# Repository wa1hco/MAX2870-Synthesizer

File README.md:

# Synthesizer
30 ro 6000 MHz frequency synthesizer based on MAX2870 chip

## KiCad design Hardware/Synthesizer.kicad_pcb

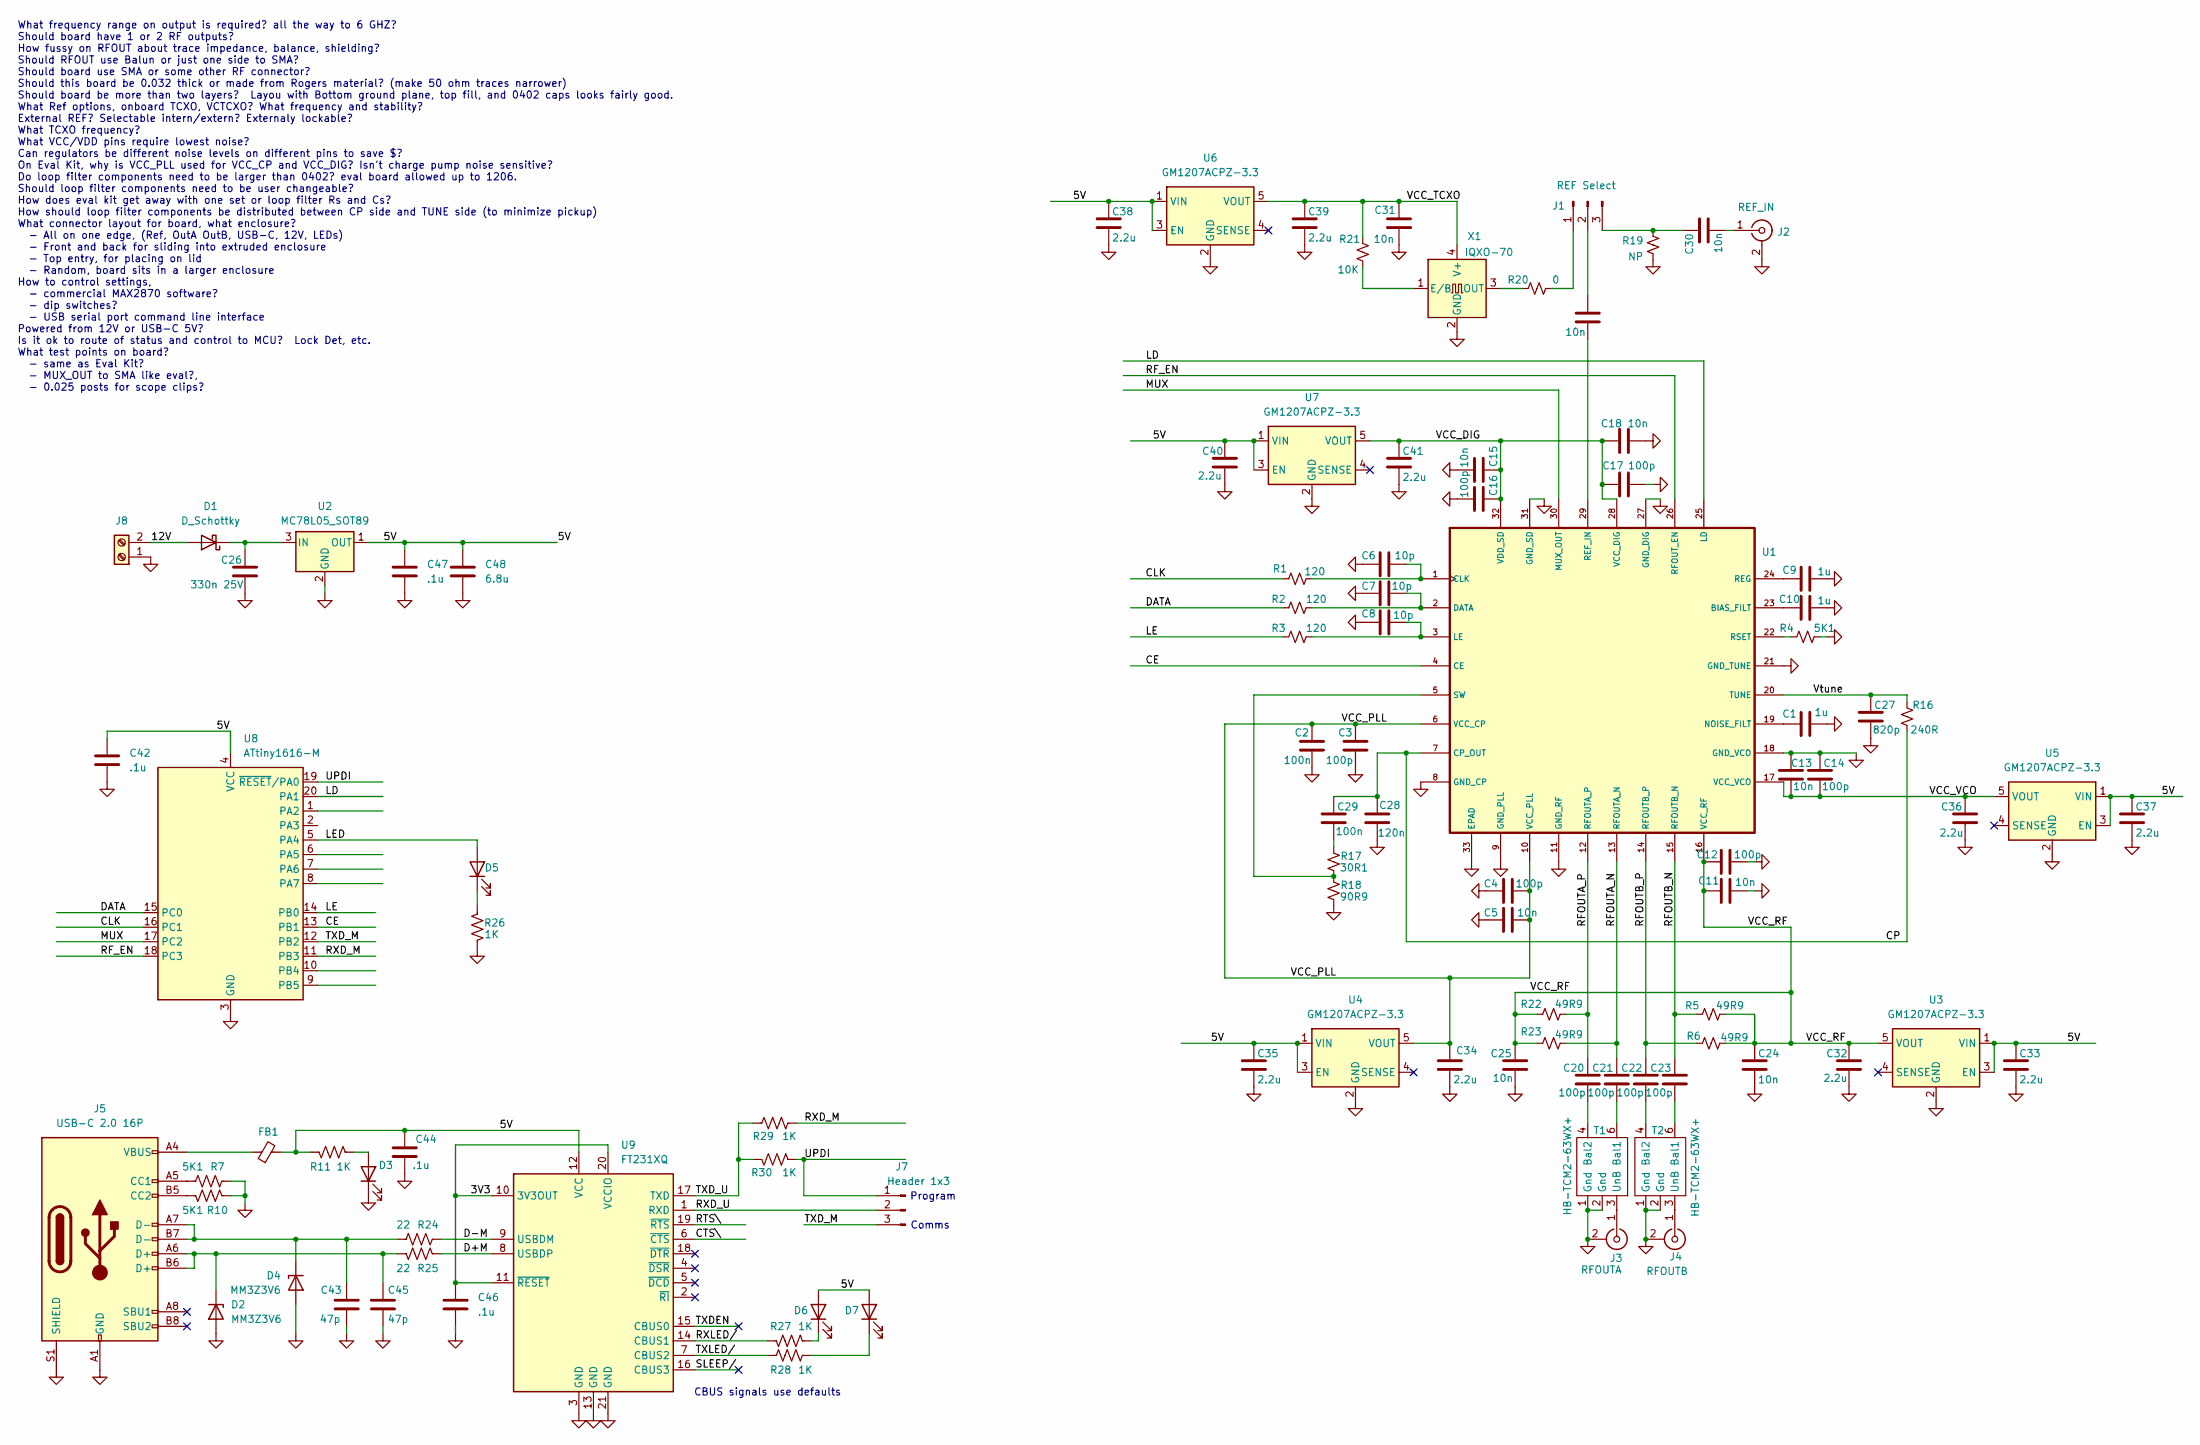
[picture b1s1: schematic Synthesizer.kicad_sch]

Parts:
C1, C9, C10: 1u; Cap_0402
C2, C29: 100n; Cap_0402
C3, C4, C12, C14, C16, C17, C20, C21, C22, C23: 100p; Cap_0402
C5, C11, C13, C15, C18, C19, C24, C25, C30, C31: 10n; Cap_0402
C6, C7, C8: 10p; Cap_0402
C26: 330n 25V; C_0603_1608Metric
C27: 820p; Cap_0402
C28: 120n; Cap_0402
C32, C33, C34, C35, C36, C37, C38, C39, C40, C41: 2.2u; Cap_0402
C42, C44, C46, C47: .1u; Cap_0402; LCSC C14663
C43, C45: 47p; Cap_0402; LCSC C1671
C48: 6.8u; C_0603_1608Metric; LCSC C338096
D1: D_Schottky; D_0603_1608Metric; LCSC C143772
D2, D4: MM3Z3V6; D_SOD-323; LCSC C116949
D3, D5: White; LED_0402_1005Metric; LCSC C2290
D6, D7: Yellow; LED_0402_1005Metric; LCSC C72038
FB1: FerriteBead_Small; L_0805_2012Metric; LCSC C1017
J1: REF Select; PinHeader_1x03_P2.54mm_Vertical; LCSC C6332196
J2: REF_IN; SMA_Samtec_SMA-J-P-H-ST-EM1_EdgeMount
J3: RFOUTA; SMA_Samtec_SMA-J-P-H-ST-EM1_EdgeMount
J4: RFOUTB; SMA_Samtec_SMA-J-P-H-ST-EM1_EdgeMount
J5: USB-C 2.0 16P; USB_C_Receptacle_G-Switch_GT-USB-7010ASV; LCSC C2988369
J7: Header 1x3; PinHeader_1x03_P2.54mm_Vertical; LCSC C6332196
J8: Screw_Terminal_01x12; TerminalBlock_TE_282834-2_1x02_P2.54mm_Horizontal; LCSC C5188451
R1, R2, R3: 120; Res_0402
R4: 5K1; Res_0402
R5, R6, R22, R23: 49R9; Res_0402
R7, R10: 5K1; Res_0402; LCSC C23186
R11, R26, R27, R28, R29, R30: 1K; Res_0402; LCSC C21190
R16: 240R; Res_0402
R17: 30R1; Res_0402
R18: 90R9; Res_0402
R19: NP; Res_0402
R20: 0; Res_0402
R21: 10K; Res_0402
R24, R25: 22; Res_0402; LCSC C23345
T1, T2: HB-TCM2-63WX+
U1: QFN-32-1EP_5x5mm_P0.5mm_EP3.1x3.1mm
U2: MC78L05_SOT89; SOT-89-3; LCSC C42738
U3, U4, U5, U6, U7: GM1207ACPZ-3.3; SOT-23-5
U8: ATtiny1616-M; VQFN-20-1EP_3x3mm_P0.4mm_EP1.7x1.7mm; LCSC C507118
U9: FT231XQ; QFN-20-1EP_4x4mm_P0.5mm_EP2.5x2.5mm; LCSC C132159
X1: IQXO-70; Oscillator_SMD_IQD_IQXO70-4Pin_7.5x5.0mm

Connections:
/3V3: C46.1, U9.10 (3V3OUT), U9.11 (~RESET), U9.20 (VCCIO)
/5V: C33.1, C35.1, C37.1, C38.1, C40.1, C42.1, C44.1, C47.1, C48.1, D6.2 (A), D7.2 (A), FB1.2, R11.2, U2.1 (OUT), U3.1 (VIN), U3.3 (EN), U4.1 (VIN), U4.3 (EN), U5.1 (VIN), U5.3 (EN), U6.1 (VIN), U6.3 (EN), U7.1 (VIN), U7.3 (EN), U8.4 (VCC), U9.12 (VCC)
/12V: D1.2 (A), J8.2
/CE: U1.4 (CE), U8.13 (PB1)
/CLK: R1.1, U8.16 (PC1)
/CP: C28.1, C29.1, R16.1, U1.7 (CP_OUT)
/CTS\: U9.6 (~CTS)
/D+M: R25.1, U9.8 (USBDP)
/D-M: R24.1, U9.9 (USBDM)
/DATA: R2.1, U8.15 (PC0)
/LD: U1.25 (LD), U8.20 (PA1)
/LE: R3.1, U8.14 (PB0)
/LED: D5.2 (A), U8.5 (PA4)
/MUX: U1.30 (MUX_OUT), U8.17 (PC2)
/RFOUTA_N: C21.1, R23.2, U1.13 (RFOUTA_N)
/RFOUTA_P: C20.1, R22.2, U1.12 (RFOUTA_P)
/RFOUTB_N: C23.1, R5.1, U1.15 (RFOUTB_N)
/RFOUTB_P: C22.1, R6.1, U1.14 (RFOUTB_P)
/RF_EN: U1.26 (RFOUT_EN), U8.18 (PC3)
/RTS\: U9.19 (~RTS)
/RXD_M: R29.2, U8.11 (PB3)
/RXD_U: J7.2, U9.1 (RXD)
/RXLED/: R27.1, U9.14 (CBUS1)
/SLEEP/: U9.16 (CBUS3)
/TXDEN: U9.15 (CBUS0)
/TXD_M: J7.3, U8.12 (PB2)
/TXD_U: R29.1, R30.1, U9.17 (TXD)
/TXLED/: R28.1, U9.7 (CBUS2)
/UPDI: J7.1, R30.2, U8.19 (~RESET/PA0)
/VCC_DIG: C15.1, C16.1, C17.1, C18.1, C41.1, U1.28 (VCC_DIG), U1.32 (VDD_SD), U7.5 (VOUT)
/VCC_PLL: C2.2, C3.2, C4.1, C5.1, C34.1, U1.6 (VCC_CP), U1.10 (VCC_PLL), U4.5 (VOUT)
/VCC_RF: C11.1, C12.1, C24.1, C25.1, C32.1, R5.2, R6.2, R22.1, R23.1, U1.16 (VCC_RF), U3.5 (VOUT)
/VCC_TCXO: C31.2, C39.1, R21.2, U6.5 (VOUT), X1.4 (V+)
/VCC_VCO: C13.1, C14.2, C36.1, U1.17 (VCC_VCO), U5.5 (VOUT)
/Vtune: C27.1, R16.2, U1.20 (TUNE)
GND: C1.2, C2.1, C3.1, C4.2, C5.2, C6.1, C7.1, C8.1, C9.2, C10.2, C11.2, C12.2, C13.2, C14.1, C15.2, C16.2, C17.2, C18.2, C24.2, C25.2, C26.2, C27.2, C28.2, C31.1, C32.2, C33.2, C34.2, C35.2, C36.2, C37.2, C38.2, C39.2, C40.2, C41.2, C42.2, C43.2, C44.2, C45.2, C46.2, C47.2, C48.2, D2.2 (A), D3.1 (K), D4.2 (A), J2.2 (Ext), J3.2 (Ext), J4.2 (Ext), J5.A1 (GND), J5.A12 (GND), J5.B1 (GND), J5.B12 (GND), J5.S1 (SHIELD), J8.1, R4.2, R7.1, R10.1, R18.2, R19.2, R26.2, T1.1 (Gnd), T1.2 (Gnd), T2.1 (Gnd), T2.2 (Gnd), U1.8 (GND_CP), U1.9 (GND_PLL), U1.11 (GND_RF), U1.18 (GND_VCO), U1.21 (GND_TUNE), U1.27 (GND_DIG), U1.31 (GND_SD), U1.33 (EPAD), U2.2 (GND), U3.2 (GND), U4.2 (GND), U5.2 (GND), U6.2 (GND), U7.2 (GND), U8.3 (GND), U8.21 (GND), U9.3 (GND), U9.13 (GND), U9.21 (GND), X1.2 (GND)
unnamed: C29.2, R17.1
unnamed: C26.1, D1.1 (K), U2.3 (IN)
unnamed: C45.1, D2.1 (K), J5.A6 (D+), J5.B6 (D+), R25.2
unnamed: D3.2 (A), R11.1
unnamed: C43.1, D4.1 (K), J5.A7 (D-), J5.B7 (D-), R24.2
unnamed: D5.1 (K), R26.1
unnamed: D6.1 (K), R27.2
unnamed: D7.1 (K), R28.2
unnamed: FB1.1, J5.A4 (VBUS), J5.A9 (VBUS), J5.B4 (VBUS), J5.B9 (VBUS)
unnamed: J1.1, R20.2
unnamed: C19.2, J1.2
unnamed: C30.1, J1.3, R19.1
unnamed: C30.2, J2.1 (In)
unnamed: J3.1 (In), T1.3 (UnB)
unnamed: J4.1 (In), T2.3 (UnB)
unnamed: J5.A5 (CC1), R7.2
unnamed: J5.B5 (CC2), R10.2
unnamed: C21.2, T1.6 (Bal1)
unnamed: C20.2, T1.4 (Bal2)
unnamed: C23.2, T2.6 (Bal1)
unnamed: C22.2, T2.4 (Bal2)
unnamed: C10.1, U1.23 (BIAS_FILT)
unnamed: C6.2, R1.2, U1.1 (CLK)
unnamed: C7.2, R2.2, U1.2 (DATA)
unnamed: C8.2, R3.2, U1.3 (LE)
unnamed: C1.1, U1.19 (NOISE_FILT)
unnamed: C19.1, U1.29 (REF_IN)
unnamed: C9.1, U1.24 (REG)
unnamed: R4.1, U1.22 (RSET)
unnamed: R17.2, R18.1, U1.5 (SW)
unnamed: R21.1, X1.1 (E/B)
unnamed: R20.1, X1.3 (OUT)

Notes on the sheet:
Comms
CBUS signals use defaults
What frequency range on output is required? all the way to 6 GHZ? Should board have 1 or 2 RF outputs? How fussy on RFOUT about trace impedance, balance, shielding? Should RFOUT use Balun or just one side to SMA? Should board use SMA or some other RF connector? Should this board be 0.032 thick or m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
Program

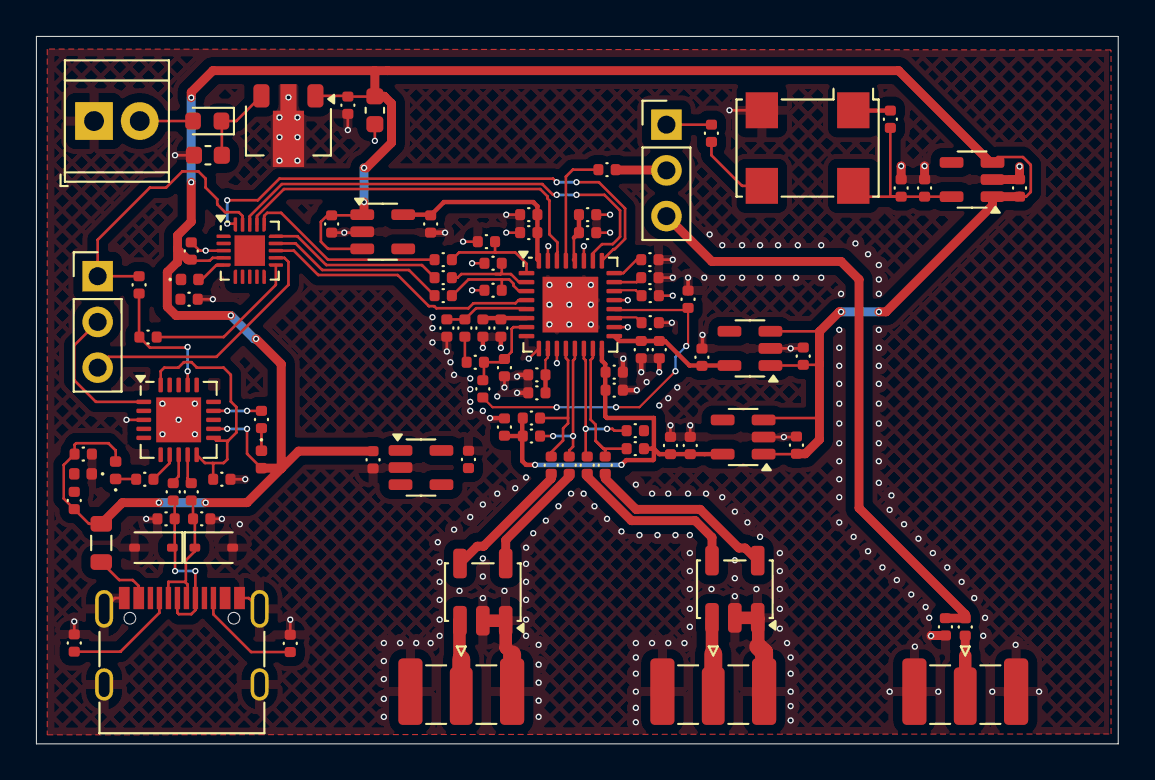
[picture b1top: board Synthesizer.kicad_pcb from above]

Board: 2 copper layers, 60.1 x 39.3 mm, 99 parts (0 on the bottom side), 64 nets.

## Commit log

2024-12-13 Start on synthesizer schematic and layout
2024-12-14 Placed the USB, Serial, ATTiny1616 and got part way through the wiring Working through the DRC issues on the PCB. Simplified the design options from the EVKIT Added user selectable jumpers
2024-12-15 Nearing completion on schematic and layout. Ready for design review.
